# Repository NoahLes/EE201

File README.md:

# Hi my name is Noah

Some of my Hobbies include Climbing, Video Games, Swimming, and Cars. I was born and raised in Seattle. I am currently a Sophmore.

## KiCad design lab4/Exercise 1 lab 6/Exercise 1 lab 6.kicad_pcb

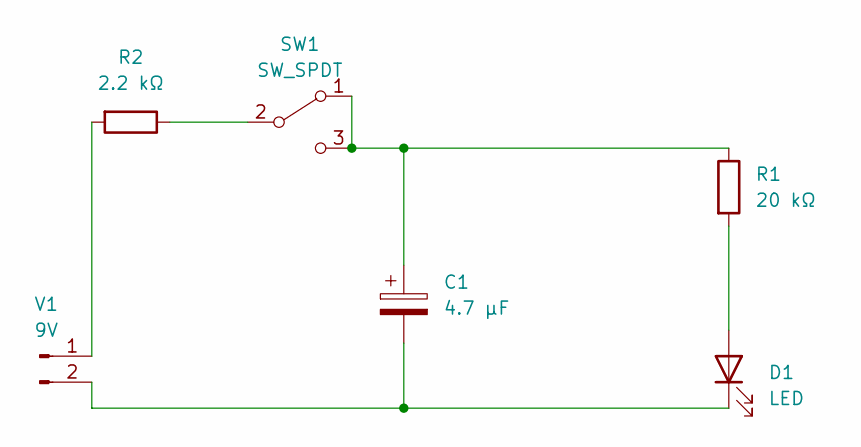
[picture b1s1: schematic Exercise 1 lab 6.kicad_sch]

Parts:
C1: 4.7 μF; C_Radial_D5.0mm_H5.0mm_P2.00mm
D1: LED; LED_D5.0mm
R1: 20 kΩ; R_Axial_DIN0516_L15.5mm_D5.0mm_P20.32mm_Horizontal
R2: 2.2 kΩ; R_Axial_DIN0516_L15.5mm_D5.0mm_P20.32mm_Horizontal
SW1: SW_SPDT; SW_E-Switch_EG1224_SPDT_Angled
V1: 9V; JST_PH_B2B-PH-K_1x02_P2.00mm_Vertical

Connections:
unnamed: C1.1, R1.1, SW1.1 (A), SW1.3 (C)
unnamed: C1.2, D1.1 (K), V1.2
unnamed: D1.2 (A), R1.2
unnamed: R2.1, SW1.2 (B)
unnamed: R2.2, V1.1

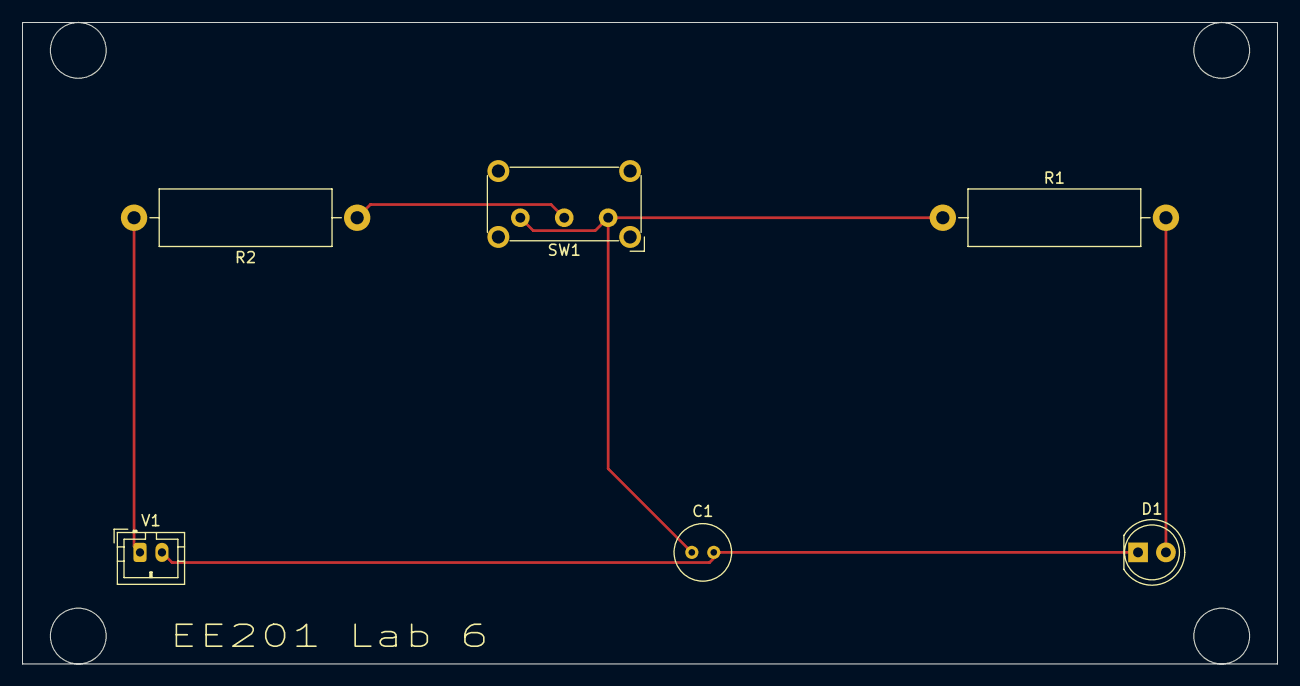
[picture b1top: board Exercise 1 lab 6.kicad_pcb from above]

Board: 2 copper layers, 114.3 x 58.4 mm, 6 parts (0 on the bottom side), 5 nets.

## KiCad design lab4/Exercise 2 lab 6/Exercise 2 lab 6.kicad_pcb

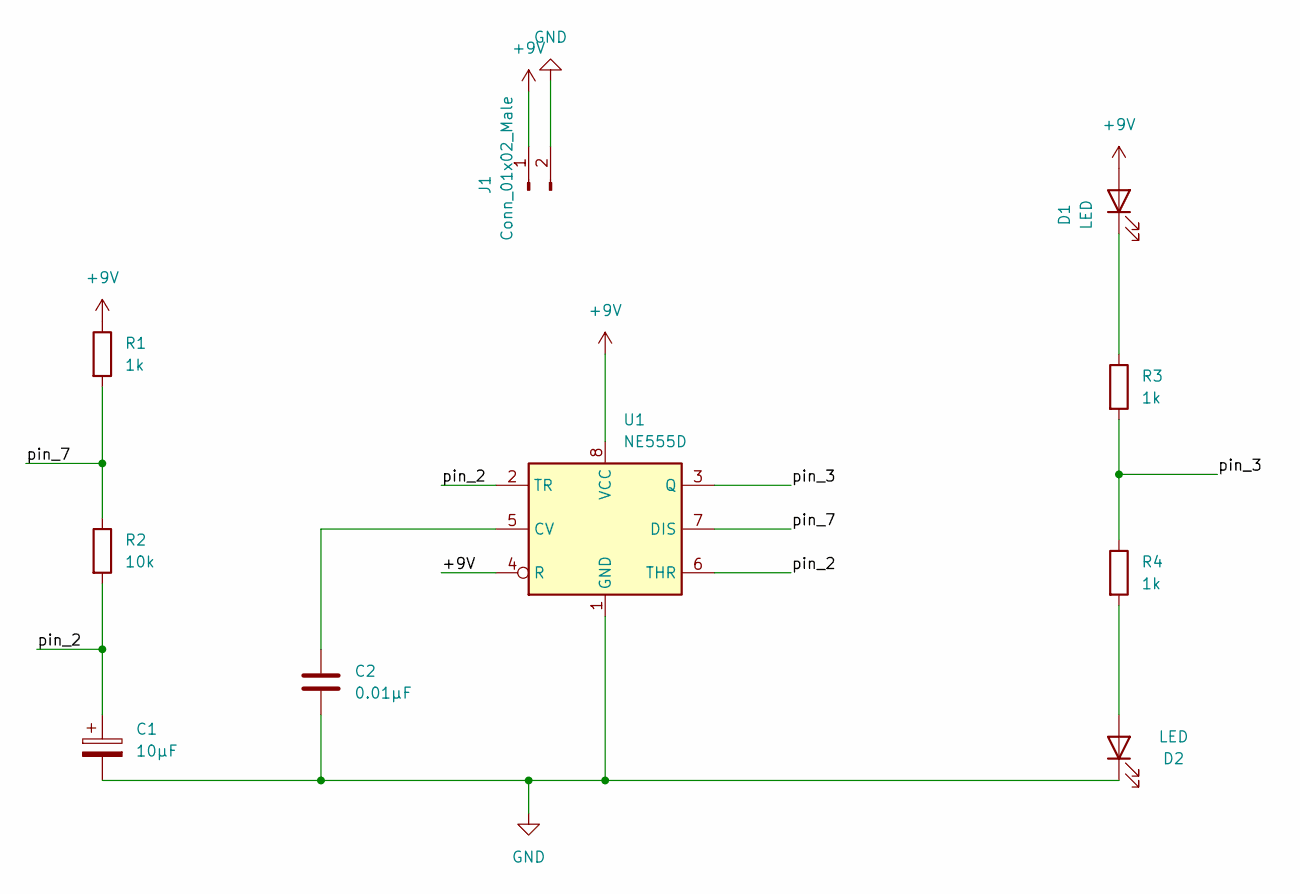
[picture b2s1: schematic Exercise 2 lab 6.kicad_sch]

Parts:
C1: 10μF; CP_EIA-3216-18_Kemet-A_Pad1.58x1.35mm_HandSolder
C2: 0.01μF; C_0805_2012Metric_Pad1.18x1.45mm_HandSolder
D1, D2: LED; LED_1206_3216Metric_Pad1.42x1.75mm_HandSolder
J1: Conn_01x02_Male; TerminalBlock_bornier-2_P5.08mm
R1, R3, R4: 1k; R_0805_2012Metric_Pad1.20x1.40mm_HandSolder
R2: 10k; R_0805_2012Metric_Pad1.20x1.40mm_HandSolder
U1: NE555D; SOIC-8-1EP_3.9x4.9mm_P1.27mm_EP2.29x3mm

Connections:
+9V: D1.2 (A), J1.1, R1.1, U1.4 (R), U1.8 (VCC)
/pin_2: C1.1, R2.2, U1.2 (TR), U1.6 (THR)
/pin_3: R3.2, R4.1, U1.3 (Q)
/pin_7: R1.2, R2.1, U1.7 (DIS)
GND: C1.2, C2.2, D2.1 (K), J1.2, U1.1 (GND)
unnamed: C2.1, U1.5 (CV)
unnamed: D1.1 (K), R3.1
unnamed: D2.2 (A), R4.2

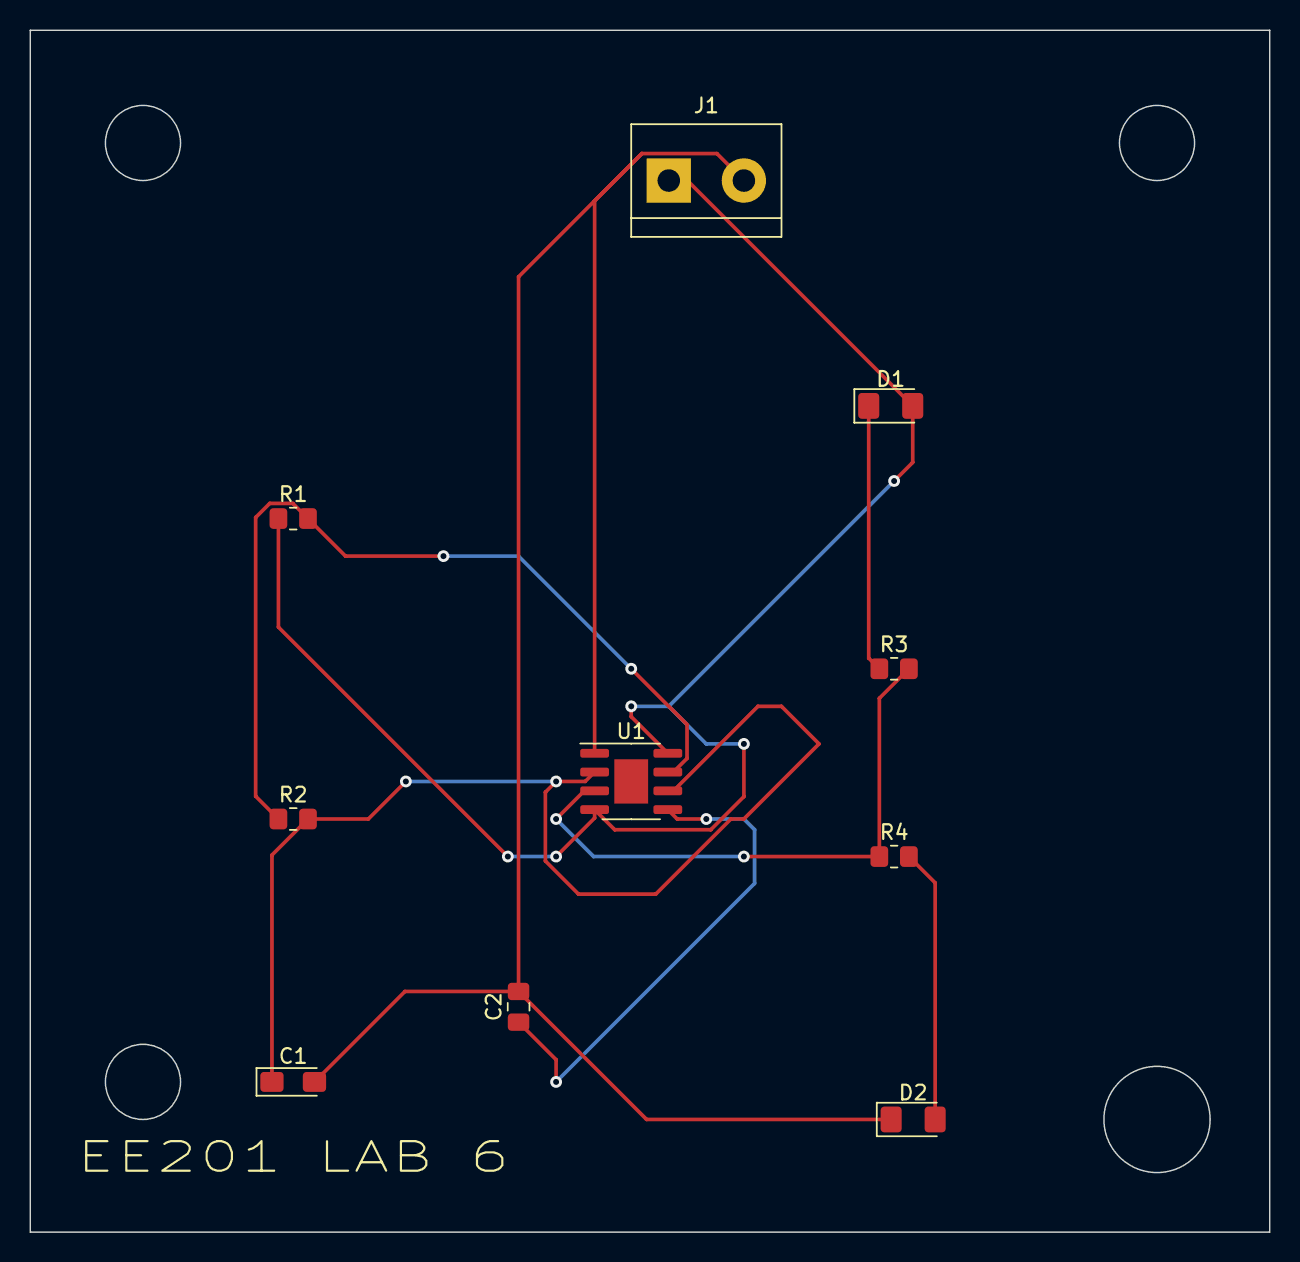
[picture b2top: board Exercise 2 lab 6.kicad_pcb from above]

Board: 2 copper layers, 83.8 x 81.3 mm, 10 parts (0 on the bottom side), 8 nets.

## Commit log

2023-01-14 This is lab #2
2023-01-14 # Hi my name is Noah
2023-01-21 Lab 3
2023-01-28 lab 4
2023-02-03 Soldering
2023-02-12 lab 6
2023-02-17 Gerber Files
2023-03-11 arduometer
